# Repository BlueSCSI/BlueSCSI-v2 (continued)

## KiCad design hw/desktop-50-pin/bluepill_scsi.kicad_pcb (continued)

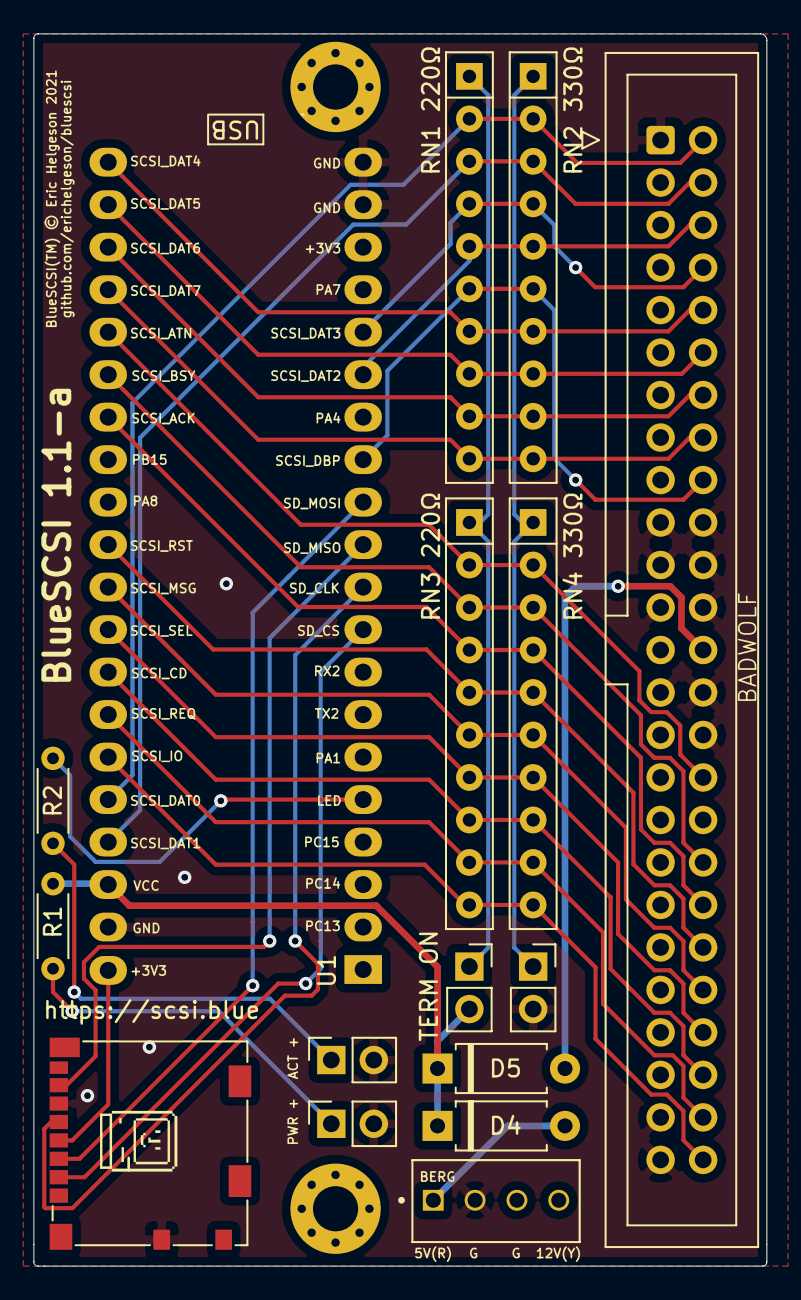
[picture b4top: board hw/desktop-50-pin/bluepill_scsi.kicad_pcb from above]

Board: 2 copper layers, 43.8 x 73.7 mm, 18 parts (0 on the bottom side), 32 nets.

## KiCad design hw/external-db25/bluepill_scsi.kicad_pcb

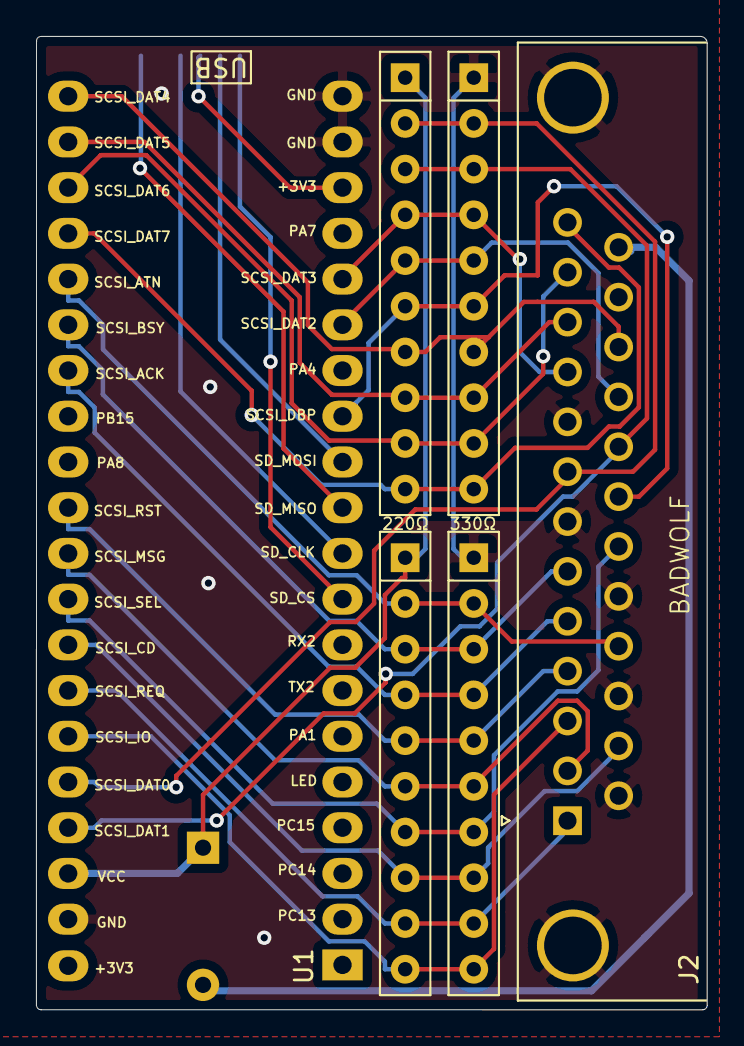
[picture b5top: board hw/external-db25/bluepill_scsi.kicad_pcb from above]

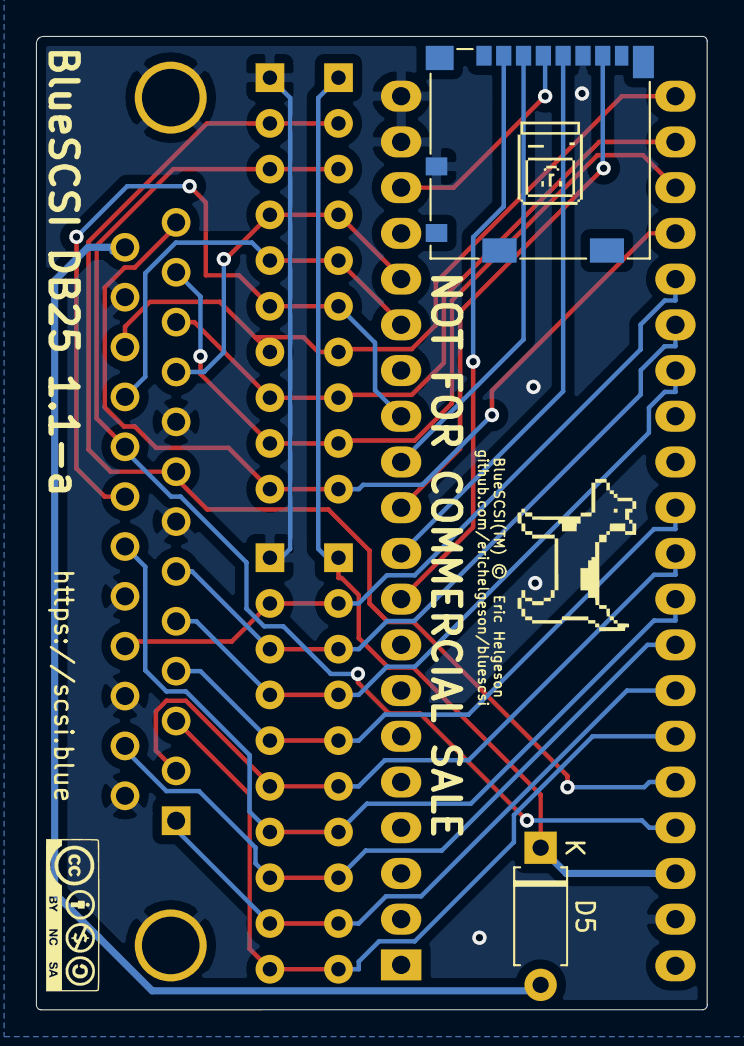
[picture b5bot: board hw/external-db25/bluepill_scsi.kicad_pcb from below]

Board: 2 copper layers, 37.3 x 54.1 mm, 11 parts (5 on the bottom side), 26 nets.

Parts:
D5: Diode; D_A-405_P7.62mm_Horizontal
G001: LOGO; dogcow
G002: LOGO; cc_by_nc_sa_front_silk_screen
G004: LOGO; mac_happy_small
J2: DB25_Male_MountingHoles; DSUB-25_Male_Horizontal_P2.77x2.84mm_EdgePinOffset4.94mm_Ho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
J5: Micro_SD_Card; microSD_HC_Molex_104031-0811
RN1, RN3: 220; R_Array_SIP10
RN2, RN4: 330; R_Array_SIP10
U1: BluePill_STM32F103C

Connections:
+3V3: J5.4, U1.18, U1.40
/SCSI_ACK: J2.5, RN3.4, RN4.4, U1.27
/SCSI_ATN: J2.17, RN3.2, RN4.2, U1.25
/SCSI_BSY: J2.6, RN3.3, RN4.3, U1.26
/SCSI_CD: J2.15, RN3.8, RN4.8, U1.33
/SCSI_DAT0: J2.8, RN1.2, RN2.2, U1.36
/SCSI_DAT1: J2.21, RN1.3, RN2.3, U1.37
/SCSI_DAT2: J2.22, RN1.5, RN2.5, U1.15
/SCSI_DAT3: J2.10, RN1.4, RN2.4, U1.16
/SCSI_DAT4: J2.23, RN1.7, RN2.7, U1.21
/SCSI_DAT5: J2.11, RN1.8, RN2.8, U1.22
/SCSI_DAT6: J2.12, RN1.9, RN2.9, U1.23
/SCSI_DAT7: J2.13, RN1.10, RN2.10, U1.24
/SCSI_DBP: J2.20, RN1.6, RN2.6, U1.13
/SCSI_IO: J2.3, RN3.10, RN4.10, U1.35
/SCSI_MSG: J2.2, RN3.6, RN4.6, U1.31
/SCSI_REQ: J2.1, RN3.9, RN4.9, U1.34
/SCSI_RST: J2.4, RN3.5, RN4.5, U1.30
/SCSI_SEL: J2.19, RN3.7, RN4.7, U1.32
/SD_CLK: J5.5, U1.10
/SD_CS: J5.2, U1.9
/SD_MISO: J5.7, U1.11
/SD_MOSI: J5.3, U1.12
/TERM_PWR: D5.2, J2.25
GND: J2.0, J2.7, J2.9, J2.14, J2.16, J2.18, J2.24, J5.6, J5.9, RN2.1, RN4.1, U1.19, U1.20, U1.39
VCC: D5.1, RN1.1, RN3.1, U1.38

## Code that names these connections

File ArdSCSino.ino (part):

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#define gpio_write(pin,val) gpio_write_bit(PIN_MAP[pin].gpio_device, PIN_MAP[pin].gpio_bit, val)
#define gpio_read(pin) gpio_read_bit(PIN_MAP[pin].gpio_device, PIN_MAP[pin].gpio_bit)

//#define DB0       PA0     // SCSI:DB0
//#define DB1       PA1     // SCSI:DB1
//#define DB2       PA2     // SCSI:DB2
//#define DB3       PA3     // SCSI:DB3
//#define DB4       PA4     // SCSI:DB4
//#define DB5       PA5     // SCSI:DB5
//#define DB6       PA6     // SCSI:DB6
//#define DB7       PA7     // SCSI:DB7
//#define DBP       PA8     // SCSI:DBP

#define ATN       PB0     // SCSI:ATN
#define BSY       PB1     // SCSI:BSY
#define ACK       PB10    // SCSI:ACK
#define RST       PB11    // SCSI:RST
#define MSG       PB5     // SCSI:MSG
#define SEL       PB6     // SCSI:SEL
#define CD        PB7     // SCSI:C/D
#define REQ       PB8     // SCSI:REQ
#define IO        PB9     // SCSI:I/O

#define SD_CS     PB12     // SDCARD:CS
#define LED       PC13     // LED

#define SCSIID    0                 // SCSI-ID 
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 */
void setup()
{
  // PA15 / PB3 / PB4 Cannot be used
  // JTAG Because it is used for debugging.
  disableDebugPorts();

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  //Port setting register (lower)
  GPIOA->regs->CRL = 0x888888888; // Configure GPIOA[8:0]

  gpio_mode(ATN, GPIO_INPUT_PU);
  gpio_mode(BSY, GPIO_INPUT_PU);
  gpio_mode(ACK, GPIO_INPUT_PU);
  gpio_mode(RST, GPIO_INPUT_PU);
  gpio_mode(SEL, GPIO_INPUT_PU);
  
  gpio_mode(MSG, GPIO_OUTPUT_PP);
  gpio_mode(CD, GPIO_OUTPUT_PP);
  gpio_mode(REQ, GPIO_OUTPUT_PP);
  gpio_mode(IO, GPIO_OUTPUT_PP);

  gpio_write(MSG, low);
  gpio_write(CD, low);
  gpio_write(REQ, low);
  gpio_write(IO, low);

  //Occurs when the RST pin state changes from HIGH to LOW
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 */
byte readHandshake(void)
{
  gpio_write(REQ, high);
  while(isLow(gpio_read(ACK))) {
    if(m_isBusReset) {
      return 0;
    }
  }
  byte r = readIO();
  gpio_write(REQ, low);
  while(isHigh(gpio_read(ACK))) {
    if(m_isBusReset) {
      return 0;
    }
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void writeHandshake(byte d)
{
  writeIO(d);
  gpio_write(REQ, high);
  while(isLow(gpio_read(ACK))) {
    if(m_isBusReset) {
      return;
    }
  }
  gpio_write(REQ, low);
  while(isHigh(gpio_read(ACK))) {
    if(m_isBusReset) {
      return;
    }
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void writeDataPhase(int len, byte* p)
{
  LOGN("DATAIN PHASE");
  gpio_write(MSG, low);
  gpio_write(CD, low);
  gpio_write(IO, high);
  for (int i = 0; i < len; i++) {
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  LOGN("DATAIN PHASE(SD)");
  uint32_t pos = adds * BLOCKSIZE;
  m_file.seek(pos);
  gpio_write(MSG, low);
  gpio_write(CD, low);
  gpio_write(IO, high);
  for(uint32_t i = 0; i < len; i++) {
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  LOGN("DATAOUT PHASE(SD)");
  uint32_t pos = adds * BLOCKSIZE;
  m_file.seek(pos);
  gpio_write(MSG, low);
  gpio_write(CD, low);
  gpio_write(IO, low);
  for(uint32_t i = 0; i < len; i++) {
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void MsgIn2(int msg)
{
  LOGN("MsgIn2");
  gpio_write(MSG, high);
  gpio_write(CD, high);
  gpio_write(IO, high);
  writeHandshake(msg);
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void MsgOut2()
{
  LOGN("MsgOut2");
  gpio_write(MSG, high);
  gpio_write(CD, high);
  gpio_write(IO, low);
  m_msb[m_msc] = readHandshake();
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void loop() 
{
  int sts = 0;
  int msg = 0;

  //BSY,SEL + is bus free
  // Selection check
  // Loop between BSY-
  if(isHigh(gpio_read(BSY))) {
    return;
  }
  // Loop while SEL is +
  if(isLow(gpio_read(SEL))) {
    return;
  }
  // BSY+ SEL-
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  LOGN("Selection");
  m_isBusReset = false;
  // Set BSY to-when selected
  gpio_mode(BSY, GPIO_OUTPUT_PP);
  gpio_write(BSY, high);
  while(isHigh(gpio_read(SEL))) {
    if(m_isBusReset) {
      goto BusFree;
    }
  }
  if(isHigh(gpio_read(ATN))) {
    bool syncenable = false;
    int syncperiod = 50;
    int syncoffset = 0;
    m_msc = 0;
    memset(m_msb, 0x00, sizeof(m_msb));
    while(isHigh(gpio_read(ATN))) {
      MsgOut2();
    }
    for(int i = 0; i < m_msc; i++) {
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  }

  LOGN("Command");
  gpio_write(MSG, low);
  gpio_write(CD, high);
  gpio_write(IO, low);
  int len;
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  }

  LOGN("Sts");
  gpio_write(MSG, low);
  gpio_write(CD, high);
  gpio_write(IO, high);
  writeHandshake(sts);
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  }

  LOGN("MsgIn");
  gpio_write(MSG, high);
  gpio_write(CD, high);
  gpio_write(IO, high);
  writeHandshake(msg);
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BusFree:
  LOGN("BusFree");
  m_isBusReset = false;
  gpio_write(REQ, low);
  gpio_write(MSG, low);
  gpio_write(CD, low);
  gpio_write(IO, low);
//  gpio_write(BSY, low);
  gpio_mode(BSY, GPIO_INPUT_PU);
}

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
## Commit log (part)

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2026-02-02 BlueSCSI Toolbox: Save some stack space
2026-02-02 Set USB product name to BlueSCSI and use standard Pico SDK PIDs
2026-02-05 Reset bus width on scsi bus reset
2026-02-08 fixup github actions with new envs
2026-02-10 ignore test dir
2026-02-10 network: Move AmigaWIFI include to scsi.c where it's needed
    Nothing in network.h needs anything from it
2026-02-15 Update framework, and fix define reference
2026-02-19 fix: prevent hang from bad CUE sheet referencing wrong/missing BIN file
    When a CUE sheet references a non-existent or mismatched BIN file,
    the device was configured with 0-size image data causing every host
    read to fail and hang the Mac during boot. This regression was
    introduced in ea61cbfdb.
    Fixes #331
2026-02-24 Add Fixed VHD image output to initiator mode
    When InitiatorVHD=1 is set in bluescsi.ini, initiator mode saves disk
    images as Fixed VHD files instead of raw .hda. A 512-byte footer
    conforming to the Microsoft VHD Image Format Specification (Oct 2006)
    is appended after the raw disk data, making images directly mountable
    by Windows, QEMU, VirtualBox, and other tools.
2026-02-24 Wait for RST to deassert before allowing new commands
2026-03-01 build: migrate from PlatformIO to CMake with Nix flake
    Replace the PlatformIO build system with CMake + Pico SDK, using a Nix
    flake for reproducible toolchain management. All 6 default firmware
    targets build successfully and produce functionally equivalent binaries.
    Build system:
    - CMakeLists.txt: Full CMake build supporting all 8 target variants
    (Pico, Pico_DaynaPORT, Pico_Audio_SPDIF, Pico_2, Pico_2_DaynaPORT,
2026-03-05 Fix scsiLogDataOut logging with NULL buffer
    scsiRead() calls scsiFinishRead(NULL, 0, ...) which then calls
    scsiLogDataOut with a NULL buffer. This breaks SCSI command logging
    and risks a NULL pointer dereference.
    Add a NULL check in scsiFinishRead() before calling scsiLogDataOut,
    and call scsiLogDataOut directly in scsiRead() with the actual
    buffer so COMMAND and OUT log messages are captured.
2026-03-12 feat: universal zip firmware update, shared bootloader log, and lastlog.txt
    Enable zip-based firmware update: firmware_update() scans for BlueSCSI_v*.zip
    on SD card, extracts the matching target .bin, and reboots into the bootloader
    which flashes it. Users drop one zip file on the SD card for any board.
    Bootloader now uses FIRMWARE_NAME_PREFIX (full target name like
    BlueSCSI_Pico_DaynaPORT) instead of FIRMWARE_PREFIX + PLATFORM_PID substring
    matching. All bootloader log messages are enabled for diagnostics.
2026-03-12 Fix stack overflow during image selection back to IMG0
    Recursion replaced by inner loop. The recursion should run once
    to get the filename for IMG0 following the last image, but causes
    stack overflow at ini_gets().
    This does not happen while loading IMG0 after reset, only during
    IMGx to IMG0 return.
2026-03-12 Reset image_directory and bin_container on SD card close
    scsiDiskCloseSDCardImages() was not closing bin_container or
    resetting image_directory, leaving stale state after SD card
    removal. This caused "Already found an image directory, skipping..."
    on SD card re-insertion.
    Move cuesheetfile.close() inside the non-ROM block alongside the
    new bin_container.close() and image_directory reset.
2026-03-12 Ignore global INI SCSI strings for network devices
    If vendor, product, and revision SCSI strings are set system-wide
    under [SCSI] in bluescsi.ini, do not apply them to DaynaPORT or
    AmigaWiFi network devices. These devices require specific SCSI
    identification strings to be recognized by their drivers.
    Per-device overrides like [SCSI4] still take effect.
2026-03-12 Defer Vdd voltage drop warnings to reduce log noise
    Delay voltage drop warnings by a configurable period (default 1s) before
    logging. Each new lower reading restarts the timer, so warnings during
    power-off are suppressed entirely as the device shuts down before the
    delay expires. Also reduces duplicate messages during brief voltage dips.
    Adds PLATFORM_VDD_WARNING_DELAY_ms define for per-platform tuning.
2026-03-12 Reduce seek overhead in CD sector reads
    Port of reinauer 5ff824acf. Reduce seek overhead in CD sector reads.
    When skip_begin == 0 (contiguous layout), perform a single seek
    before the transfer loop instead of seeking per-sector. The
    existing per-sector seek path is preserved as fallback for
    non-contiguous layouts.
2026-03-15 fix: add missing cdrom_track_end_lba resets in CUE sheet paths
    Two code paths in scsiDiskOpenHDDImage() reset cdrom_trackinfo via
    memset but did not reset the companion cdrom_track_end_lba field,
    potentially leaving stale track boundary data after CD image change
    or folder-based CUE sheet initialization.
2026-03-15 logging: Add missing 12- and 16-byte command names
    Cherry-picked from cefacd455.
2026-03-15 build: nix flake update
2026-03-16 fix: stack overflow crash on RP2350 during image init
2026-03-18 fix: Restore WiFi (DaynaPORT) for CMake build on all Pico W variants
    After migrating from PlatformIO to CMake, WiFi was broken because the
    CYW43 driver is now compiled from source instead of using a GCC 11
    precompiled library. Multiple issues fixed:
    CMake configuration:
    - Add PICO_CYW43_SUPPORTED=1 to all WiFi targets (SDK board CMake
    doesn't propagate this to our compile definitions)
2026-03-30 fix: USB MSC initiator mode no longer overrides hardware switch when SD absent
2026-03-30 as400: Add AS/400 (iSeries) SCSI device emulation support
    Add System = AS400 preset (Ultra/Ultra Wide only) with Write Same(10),
    Skip Read/Write(10) vendor commands, custom VPD/SPD inquiry responses
    via INI, AS/400-specific REQUEST SENSE format, unit attention on
    power-on/reset, and 13-second spin-up delay.
    Squashed from yyzkevin/as400 branch (6690a24..44b6b76).
    Works and can IPL.
2026-03-30 build: upgrade GitHub Actions to Node.js 24 compatible versions
2026-04-02 fix: tape READ BLOCK LIMITS and SPACE CDB byte extraction bugs
    READ BLOCK LIMITS (0x05): data[5] duplicated data[4] instead of
    containing the LSB of minimum block length. For 512-byte blocks this
    reported min=0x0202 instead of 0x0200.
    (SCSI-2 Section 10.2.4)
    SPACE (0x11): count was extracted as 32-bit from CDB[2-5] with wrong
    shifts, including the control byte as data. Fixed to 24-bit extraction
2026-04-04 as400: backport MODE SENSE, LOG SENSE, VPD defaults, wide SCSI fix, and RESERVE/RELEASE
    Backport AS/400 enhancements from b8b49eb14 adapted for
    BlueSCSI's architecture:
    - Fix wide SCSI odd-byte DATA_OUT: round up count when odd to complete
    the final 16-bit read (fixes skip mask corruption)
    - Accept extent reservations (RESERVE/RELEASE) for AS/400 quirks
    - Return captured IBM drive MODE SENSE all-pages (0x3F) response
2026-04-04 toolbox: rename SET_UPLOAD_DIR to SET_WORKING_DIR, add GET_WORKING_DIR
    Rename SET_UPLOAD_DIR to SET_WORKING_DIR since it controls the working
    directory for all file operations, not just uploads. On-wire values
    unchanged (subcommand 0x02, capability bit 0x04).
    Add GET_WORKING_DIR (subcommand 0x03) which returns the current
    effective directory as a null-terminated string. Returns the override
    if set, otherwise the default from bluescsi.ini.
2026-04-05 ci: enable cachix push with auth token
2026-04-13 build: Add macOS support and fix build gotchas
2026-04-17 log: decode SD card OID as ASCII and add manufacturer name
2026-04-18 MODE SENSE: Add Notch and Partition page (0Ch)
    Add mode page 0Ch (Notch and Partition) per SCSI-2 section 9.3.3.5,
    Table 167. This optional page defines notch parameters for rigid disk
    drives with variable blocks per cylinder.
    All fields are zero, indicating a non-notched drive, which provides
    maximum compatibility. Only returned for SCSI-2 mode direct-access
    devices (excluded from optical and sequential).
2026-04-18 scsi: WRITE to read-only media returns DATA_PROTECT sense key
    Per SCSI-2 §9.1.12 (Error reporting) and Table 69, WRITE PROTECTED
    (ASC 0x2700) pairs with sense key DATA_PROTECT (0x07), not
    ILLEGAL_REQUEST (0x05). Some hosts branch on the sense key to
    distinguish 'you passed a bad CDB' from 'the media is write-protected'
    and will retry incorrectly if we report the former.
2026-04-21 dist: Add note to zip file for users
2026-04-27 log: widen DebugLogMask to cover wide SCSI IDs 8-15
    The log mask was a uint8_t defaulting to 0xFF with the selected ID
    masked by & 7, so any future build with S2S_MAX_TARGETS > 8 would
    silently drop debug logging for IDs 8-15. Introduce
    BLUESCSI_DEFAULT_LOG_MASK = ((1UL << S2S_MAX_TARGETS) - 1UL), widen
    g_scsi_log_mask to uint32_t, and mask the selected ID by
    (S2S_MAX_TARGETS - 1) so the mask tracks target count automatically.
2026-04-27 initiator: extract peripheralTypeName helper for testability
2026-04-28 printer: emulate Apple LaserWriter IISC SCSI printer
    Adds device type S2S_CFG_PRINTER. A PR<id>/ folder on the SD card
    registers a printer at that SCSI ID and doubles as the spool target;
    captured jobs land in /PR<id>/print_NNNN.bin as a stream of CDB +
    length-prefixed payload records.
    print files can be converted here: https://bluescsi.com/printer
    Thanks to demik for the reverse-engineering documentation:
2026-04-28 as400: update MODE SENSE blob with more complete drive capture
    Replace the 140-byte MODE SENSE all-pages response with a more
    complete 221-byte capture from a different IBM drive. Includes
    additional pages 0x89, 0x8C, 0x10, 0x9A, 0x9C.
2026-04-28 as400: skip inquiry defaults for non-fixed device types
2026-04-28 as400: add AS400_DiskPartNumber INI key with EBCDIC injection
    The AS/400 VPD 0x01 default bakes in a specific IBM FRU (09L4044 — a
    captured 9406-170 DASD feature code). Operators emulating any other
    DASD SKU (4326, 4327, later iSeries FRUs in the 09L*, 97P*, 21P* spaces)
    had no ergonomic override path; the only workaround was hand-rolling a
    full vpd01= hex string plus the CP037 EBCDIC translation by hand.
    Add AS400_DiskPartNumber per [SCSI<n>] section. Up to 7 ASCII chars,
2026-04-28 as400: rename AS400_DiskSerial INI key to AS400_DiskSerialNumber
    The AS/400 per-ID INI keys had inconsistent naming: the part-number key
    was spelled AS400_DiskPartNumber (ends in 'Number') while the serial key
    was spelled AS400_DiskSerial (no 'Number' suffix). Rename the serial key
    so both keys follow the same AS400_Disk<Thing>Number pattern. Update the
    ini_gets() call and the code comments that still referenced the older
    name. No behavior change beyond the key name.
2026-04-29 vhd: load VHD files as emulated SCSI targets
2026-04-30 as400: default toolbox off under AS400 system preset for now
2026-05-05 build: rename combined V2 DaynaPORT UF2 to BlueSCSI_V2_Universal
2026-05-09 Add PC-9801-55 system preset
2026-06-09 panel: enable I2C panel on RAM-capable v2 profiles
